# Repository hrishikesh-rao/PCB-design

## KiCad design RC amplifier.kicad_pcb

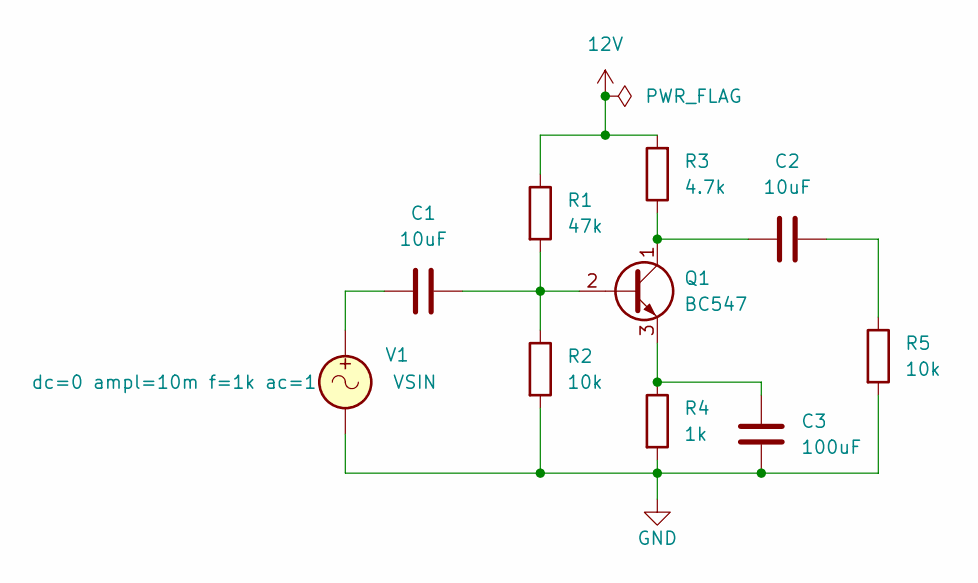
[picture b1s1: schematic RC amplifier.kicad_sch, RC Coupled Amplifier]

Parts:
C1, C2: 10uF; CP_Radial_D6.3mm_P2.50mm
C3: 100uF; CP_Radial_D6.3mm_P2.50mm
Q1: BC547; TO-92_Inline
R1: 47k; R_Axial_DIN0207_L6.3mm_D2.5mm_P7.62mm_Horizontal
R2, R5: 10k; R_Axial_DIN0207_L6.3mm_D2.5mm_P7.62mm_Horizontal
R3: 4.7k; R_Axial_DIN0207_L6.3mm_D2.5mm_P7.62mm_Horizontal
R4: 1k; R_Axial_DIN0207_L6.3mm_D2.5mm_P7.62mm_Horizontal
V1: VSIN

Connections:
12V: R1.1, R3.2
GND: C3.2, R2.2, R4.2, R5.2, V1.2
unnamed: C1.1, V1.1
unnamed: C2.2, R5.1
unnamed: C1.2, Q1.2 (B), R1.2, R2.1
unnamed: C2.1, Q1.1 (C), R3.1
unnamed: C3.1, Q1.3 (E), R4.1

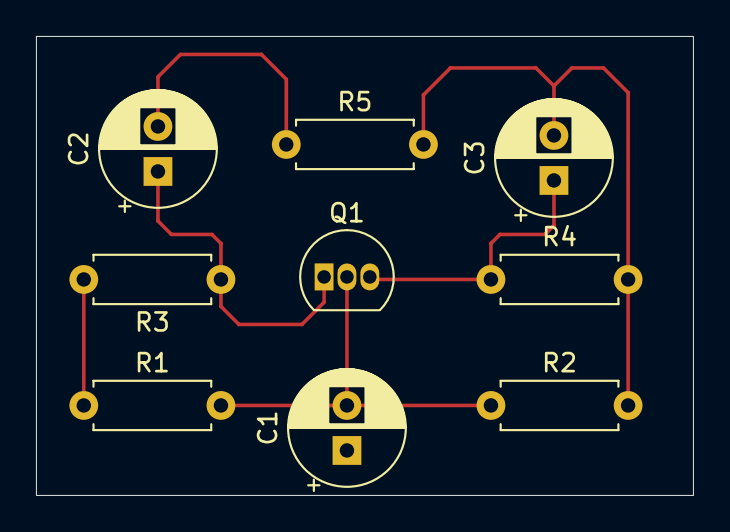
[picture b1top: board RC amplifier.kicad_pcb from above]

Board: 2 copper layers, 36.5 x 25.5 mm, 9 parts (0 on the bottom side), 6 nets.

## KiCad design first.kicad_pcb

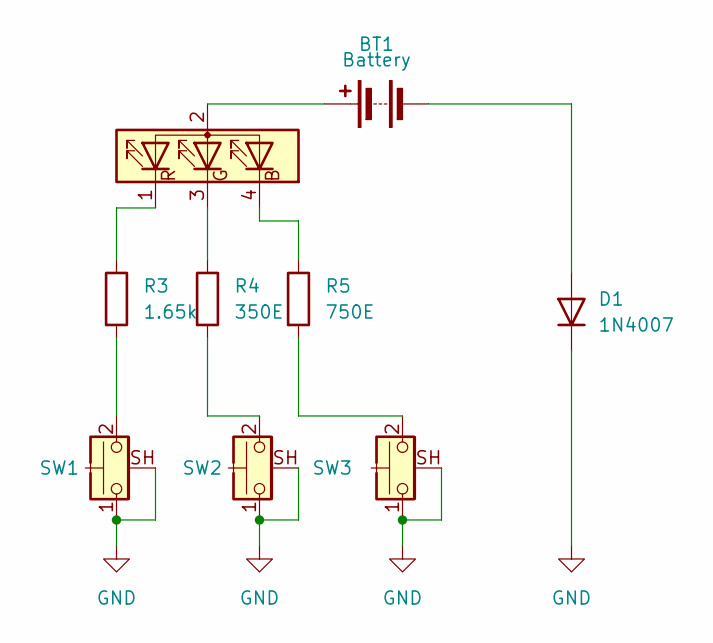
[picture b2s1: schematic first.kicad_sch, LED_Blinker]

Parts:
BT1: Battery; BatteryHolder_Keystone_2479_3xAAA
D1: 1N4007; D_DO-41_SOD81_P10.16mm_Horizontal
D4: APFA3010; LED_Kingbright_APFA3010_3x1.5mm_Horizontal
R3: 1.65k; R_0612_1632Metric
R4: 350E; R_0612_1632Metric
R5: 750E; R_0612_1632Metric
SW1, SW2, SW3: CK_KMS2xxG; SW_SPST_CK_KMS2xxGP

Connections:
GND: D1.1 (K), SW1.1, SW1.SH (B), SW2.1, SW2.SH (B), SW3.1, SW3.SH (B)
unnamed: BT1.1 (+), D4.2 (A)
unnamed: BT1.2 (-), D1.2 (A)
unnamed: D4.4 (B), R5.1
unnamed: D4.3 (G), R4.1
unnamed: D4.1 (R), R3.1
unnamed: R3.2, SW1.2
unnamed: R4.2, SW2.2
unnamed: R5.2, SW3.2

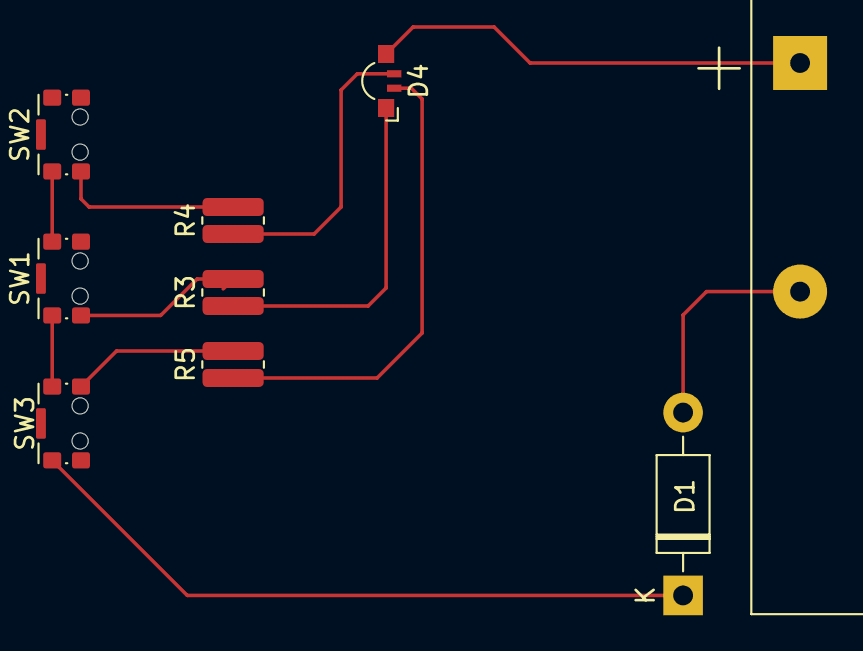
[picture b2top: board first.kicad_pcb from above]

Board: 2 copper layers, 9 parts (0 on the bottom side), 9 nets.

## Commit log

2026-02-28 Add files via upload
    Schematic and pcb
2026-02-28 Add files via upload
    RGB led control system
2026-03-09 Create RC amplifier
2026-03-17 Add files via upload
    rc amplifier
